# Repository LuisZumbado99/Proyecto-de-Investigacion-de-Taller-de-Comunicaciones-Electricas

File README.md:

# Proyecto Integral de Investigación y Diseño - Taller de Comunicaciones Eléctricas

Este repositorio contiene la Prueba de Concepto (PoC) y el desarrollo completo de un proyecto de ingeniería enfocado en las áreas de **Integridad de Señal (SI)**, **Integridad de Potencia (PI)** o **Compatibilidad/Interferencias Electromagnéticas (EMC/EMI)**.

## Metodología
Desarrollado bajo el marco de trabajo **CDIO** (*Concebir, Diseñar, Implementar, Operar*) y la metodología de **Aprendizaje Basado en Problemas (PBL)**.

## Toolchain de Código Abierto
El proyecto utiliza un entorno de herramientas multiplataforma (disponible en Linux, Windows y macOS):

* **Diseño esquemático y PCB:** KiCad
* **Simulación electromagnética (Full-Wave 3D):** openEMS
* **Simulación circuital:** NGspice / Qucs-s
* **Procesamiento y análisis:** Python (`scikit-rf`)

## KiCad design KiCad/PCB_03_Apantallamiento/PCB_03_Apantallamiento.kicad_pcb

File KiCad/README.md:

# Diseño de PCB en KiCad — Técnicas de aislamiento electromagnético

## Descripción

Este repositorio contiene el diseño de cuatro placas de circuito impreso (PCB) desarrolladas en **KiCad 9** para estudiar diferentes técnicas pasivas de reducción del acoplamiento electromagnético (*crosstalk*) entre líneas de transmisión y recepción (TX/RX).

Se diseñaron cuatro configuraciones utilizando la misma geometría base, conectores SMA y sustrato dieléctrico, con el propósito de comparar las técnicas de aislamiento.

## Diseños de PCB

| PCB | Nombre | Descripción |
|---|---|---|
| 01 | PCB_01_Base | Dos pistas paralelas sin aislamiento adicional |
| 02 | PCB_02_ViaFencing | Pistas con barreras de vías conectadas a GND |
| 03 | PCB_03_Apantallamiento | Pistas con conexiones para una pantalla metálica |
| 04 | PCB_04_ViaFencing_Apantallamiento | Combinación de ambas técnicas |

### PCB 01 — Diseño base

- Dos líneas de transmisión: TX y RX.
- Cuatro conectores SMA de montaje en borde.
- Plano de tierra en B.Cu.
- Dos pistas con transiciones diagonales de 45°.
- Separación de 2 mm entre bordes en el tramo central.

### PCB 02 — Via Fencing

Se incorporaron barreras de vías conectadas a GND alrededor de las pistas.

- Tres filas longitudinales de vías.
- Nueve vías adicionales.
- Separación longitudinal de 7.84 mm entre centros.
- Diámetro de vía: 0.80 mm.
- Perforación: 0.40 mm.
- Franjas de conexión GND en F.Cu.

### PCB 03 — Apantallamiento

Se preparó una estructura para incorporar una pantalla metálica sobre la línea TX.

- Seis vías GND adicionales.
- Dos franjas de conexión GND.
- Contorno mecánico de referencia en User.Drawings.
- Longitud propuesta de pantalla: 23 mm.
- Ancho propuesto: 2.5 mm.
- Altura propuesta: 2 mm sobre F.Cu.

**Nota:** la cubierta metálica elevada todavía no está incorporada físicamente al diseño. El contorno de User.Drawings representa únicamente su ubicación propuesta.

### PCB 04 — Técnicas combinadas

Se integraron las conexiones del apantallamiento y las barreras de vías.

- Tres filas de vías GND.
- Separación longitudinal de 7.84 mm.
- Franjas de conexión en F.Cu.
- Contorno de referencia para la pantalla metálica.
- Plano de tierra común en B.Cu.

## Especificaciones de diseño

| Parámetro | Valor |
|---|---|
| Software | KiCad 9 |
| Dimensiones de PCB | 40 × 50 mm |
| Capas de cobre | 2 |
| Material del sustrato | Rogers RO4350B |
| Espesor del dieléctrico | 0.508 mm |
| Permitividad relativa | 3.66 |
| Espesor de cobre | 0.035 mm por capa |
| Ancho de pistas | 0.508 mm |
| Longitud objetivo de pistas | 40 mm |
| Separación central entre pistas | 2 mm entre bordes |
| Conectores | 4 SMA Edge Mount |
| Diámetro de vías | 0.80 mm |
| Perforación de vías | 0.40 mm |
| Separación longitudinal de vías | 7.84 mm |

## Organización de archivos

```text
KiCad_PCB/
├── README.md
├── PCB_01_Base/
│   ├── PCB_01_Base.kicad_pro
│   ├── PCB_01_Base.kicad_sch
│   └── PCB_01_Base.kicad_pcb
│
├── PCB_02_ViaFencing/
│   ├── PCB_02_ViaFencing.kicad_pro
│   ├── PCB_02_ViaFencing.kicad_sch
│   └── PCB_02_ViaFencing.kicad_pcb
│
├── PCB_03_Apantallamiento/
│   ├── PCB_03_Apantallamiento.kicad_pro
│   ├── PCB_03_Apantallamiento.kicad_sch
│   └── PCB_03_Apantallamiento.kicad_pcb
│
└── PCB_04_ViaFencing_Apantallamiento/
    ├── PCB_04_ViaFencing_Apantallamiento.kicad_pro
    ├── PCB_04_ViaFencing_Apantallamiento.kicad_sch
    └── PCB_04_ViaFencing_Apantallamiento.kicad_pcb
```

## Cómo abrir los diseños

1. Instalar KiCad 9.
2. Descargar o clonar este repositorio.
3. Abrir KiCad.
4. Seleccionar el archivo `.kicad_pro` de la PCB deseada.
5. Abrir el editor PCB para visualizar las pistas, los conectores y las estructuras de aislamiento.

Los diseños utilizan una biblioteca personalizada de huellas SMA denominada `RF_SubGHz`. Esta biblioteca debe estar disponible y correctamente vinculada al proyecto para editar o actualizar las huellas.

## Verificación de diseño

Los diseños fueron revisados mediante el comprobador de reglas de diseño (DRC) de KiCad.

Se verificaron las conexiones TX, RX y GND, así como la separación entre conductores.

Las violaciones asociadas al montaje en borde de los conectores SMA se trataron como exclusiones específicas. Su compatibilidad con los requisitos de fabricación debe confirmarse antes de producir las placas.

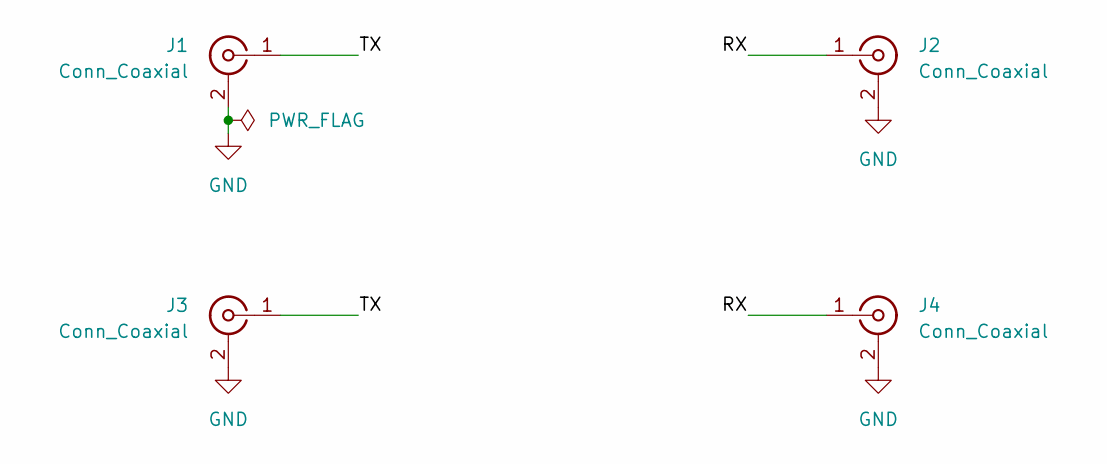
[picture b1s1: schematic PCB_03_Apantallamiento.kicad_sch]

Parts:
J1, J2, J3, J4: Conn_Coaxial; SMA_WOKEN_00201CA2GP904N_EdgeMount

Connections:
/RX: J2.1 (In), J4.1 (In)
/TX: J1.1 (In), J3.1 (In)
GND: J1.2 (Ext), J2.2 (Ext), J3.2 (Ext), J4.2 (Ext)

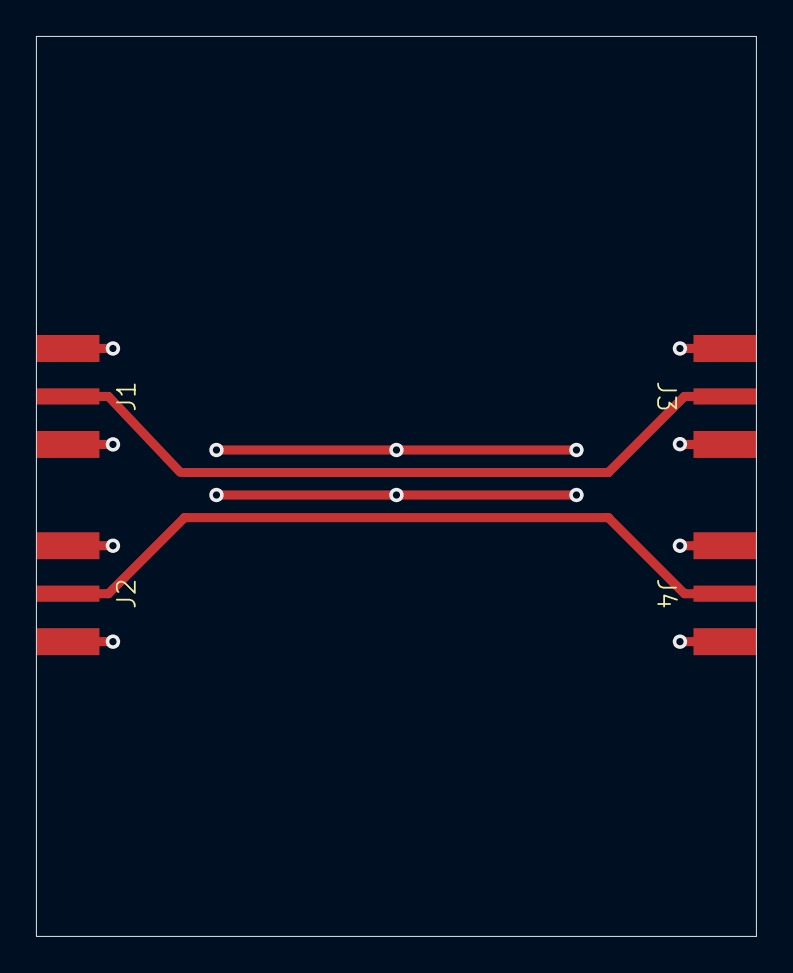
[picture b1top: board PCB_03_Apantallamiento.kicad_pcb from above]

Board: 2 copper layers, 40.0 x 50.0 mm, 4 parts (0 on the bottom side), 3 nets.

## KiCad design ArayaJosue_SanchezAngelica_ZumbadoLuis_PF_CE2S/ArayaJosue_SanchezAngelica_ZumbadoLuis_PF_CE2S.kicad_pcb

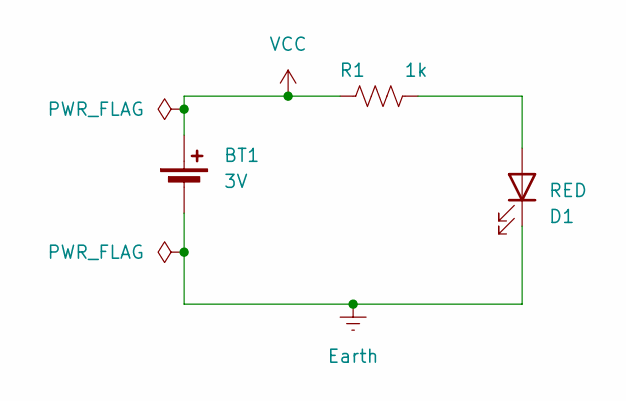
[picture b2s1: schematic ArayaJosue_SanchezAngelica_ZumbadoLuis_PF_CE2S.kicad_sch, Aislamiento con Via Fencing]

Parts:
BT1: 3V; BatteryHolder_Keystone_1058_1x2032
D1: RED; LED_D5.0mm
R1: 1k; R_Axial_DIN0309_L9.0mm_D3.2mm_P12.70mm_Horizontal

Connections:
Earth: BT1.2 (-), D1.1 (K)
unnamed: D1.2 (A), R1.2
VCC: BT1.1 (+), R1.1

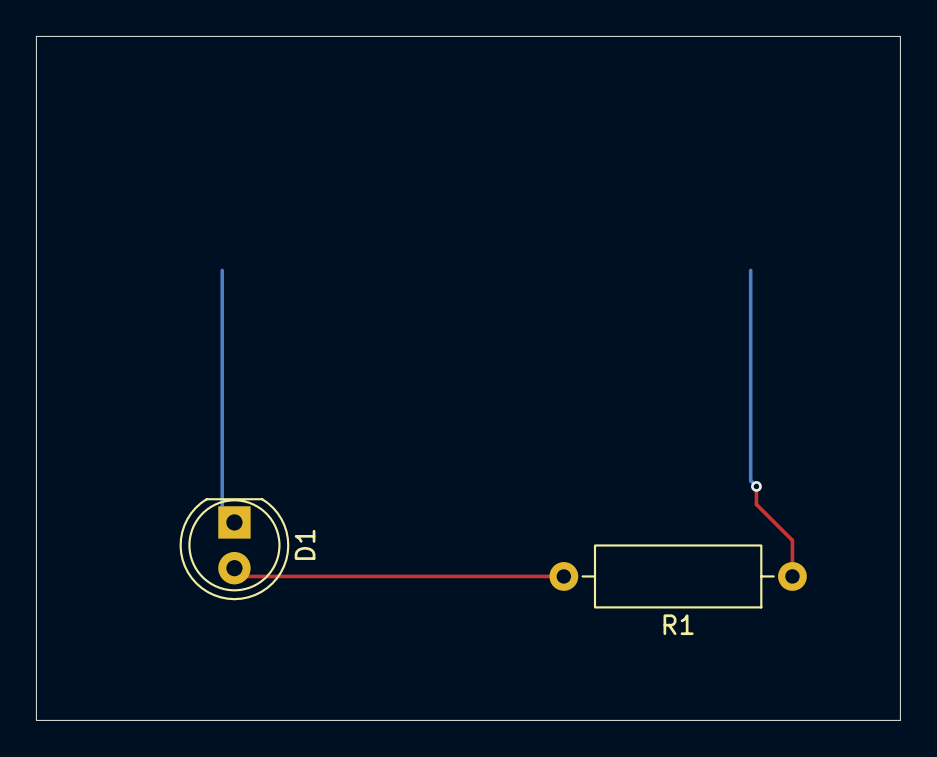
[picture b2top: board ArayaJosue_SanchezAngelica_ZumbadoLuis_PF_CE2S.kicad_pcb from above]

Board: 2 copper layers, 48.0 x 38.0 mm, 3 parts (1 on the bottom side), 3 nets.
